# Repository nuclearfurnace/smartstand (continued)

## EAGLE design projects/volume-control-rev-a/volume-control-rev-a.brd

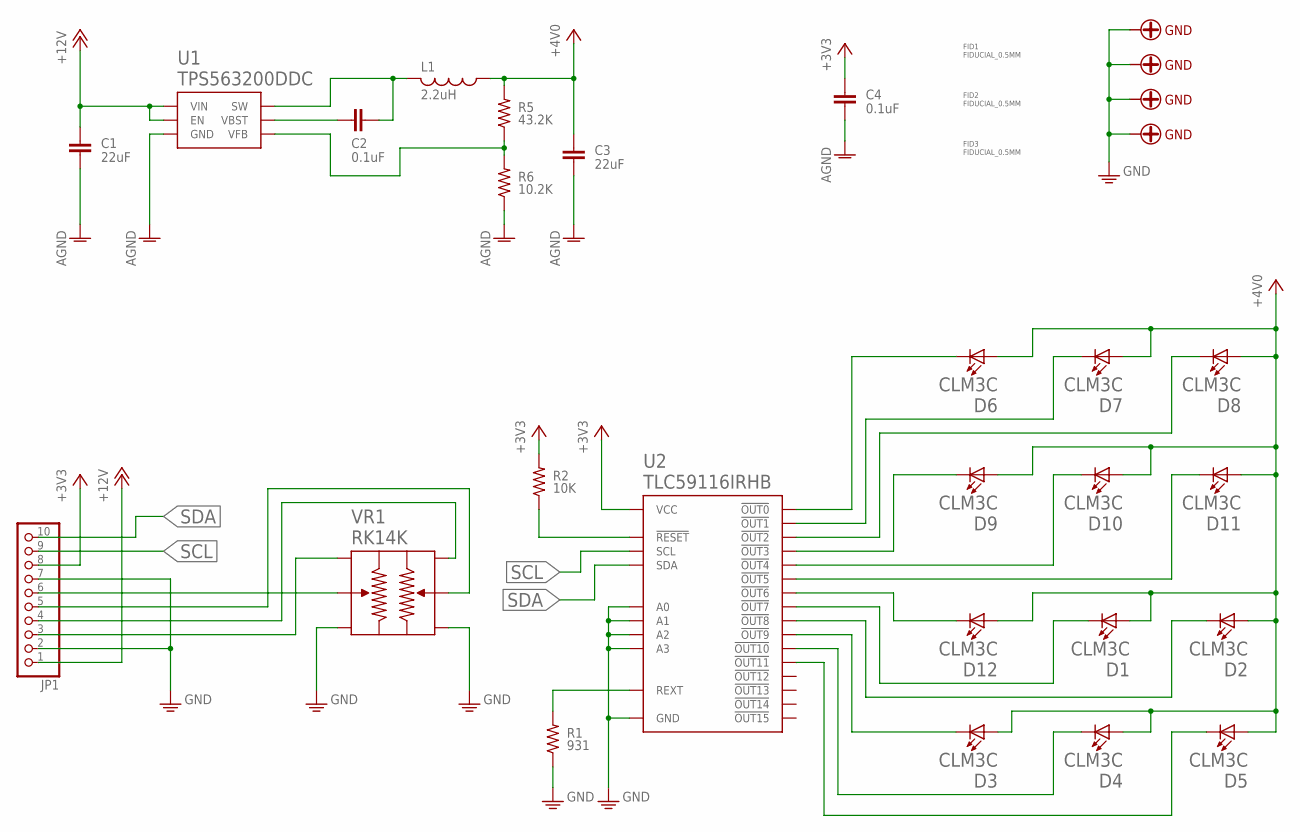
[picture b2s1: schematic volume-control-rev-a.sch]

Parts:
AGND: SCREW-THRU-GND-#4
C1, C3: 22uF; C1210
C2: 0.1uF; C0603
C4: 0.1uF; C0402
D1, D2, D3, D4, D5, D6, D7, D8, D9, D10, D11, D12: CLM3C; PLCC-2; MPN CLM3C-WKW-CXAYA453
FID1, FID2, FID3: FIDUCIAL_0.5MM
JP1: PINHD-1X10; 1X10; MPN 22-05-3101
L1: 2.2uH; COILCRAFT-XFL4020; MPN XFL4020-222MEB
R1: 931; R0402
R2: 10K; R0402
R5: 43.2K; R0402
R6: 10.2K; R0402
U1: TPS563200DDC; R-PDSO-G6-DBV; MPN TPS563200DDCT
U2: TLC59116IRHB; S-PVQFN-N32-RHB; MPN TLC59116IRHB
U$2, U$3, U$4: SCREW-THRU-GND-#4
VR1: RK14K

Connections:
+3V3: C4.1, JP1.8, R2.2, U2.P$27 (VCC)
+4V0: C3.1, D1.ANODE (A), D2.ANODE (A), D3.ANODE (A), D4.ANODE (A), D5.ANODE (A), D6.ANODE (A), D7.ANODE (A), D8.ANODE (A), D9.ANODE (A), D10.ANODE (A), D11.ANODE (A), D12.ANODE (A), L1.P$1 (1), R5.2
+12V: C1.1, JP1.1, U1.3 (VIN), U1.5 (EN)
AGND: C1.2, C3.2, C4.2, R6.1, U1.1 (GND)
GND: AGND.P$1, AGND.P$2, AGND.P$3, AGND.P$4, AGND.P$5, AGND.P$6, AGND.P$7, AGND.P$8, AGND.P$9, JP1.2, JP1.7, R1.1, U2.P$1 (A2), U2.P$2 (A3), U2.P$7 (GND), U2.P$18 (GND), U2.P$23 (GND), U2.P$31 (A0), U2.P$32 (A1), U2.P$EP (GND), U2.P$EP1 (GND), U2.P$EP2 (GND), U2.P$EP3 (GND), U2.P$EP4 (GND), U2.P$EP5 (GND), U$2.P$1, U$2.P$2, U$2.P$3, U$2.P$4, U$2.P$5, U$2.P$6, U$2.P$7, U$2.P$8, U$2.P$9, U$3.P$1, U$3.P$2, U$3.P$3, U$3.P$4, U$3.P$5, U$3.P$6, U$3.P$7, U$3.P$8, U$3.P$9, U$4.P$1, U$4.P$2, U$4.P$3, U$4.P$4, U$4.P$5, U$4.P$6, U$4.P$7, U$4.P$8, U$4.P$9, VR1.L3 (OUT_L), VR1.R3 (OUT_R)
LEFT_IN: JP1.3, VR1.L1 (IN_L)
LEFT_OUT: JP1.6, VR1.L2 (WIPER_L)
unnamed: D6.CATHODE (C), U2.P$3 (!OUT0)
unnamed: D7.CATHODE (C), U2.P$4 (!OUT1)
unnamed: D8.CATHODE (C), U2.P$5 (!OUT2)
unnamed: D3.CATHODE (C), U2.P$15 (!OUT9)
unnamed: D4.CATHODE (C), U2.P$16 (!OUT10)
unnamed: D5.CATHODE (C), U2.P$17 (!OUT11)
unnamed: D9.CATHODE (C), U2.P$6 (!OUT3)
unnamed: D10.CATHODE (C), U2.P$8 (!OUT4)
unnamed: D11.CATHODE (C), U2.P$9 (!OUT5)
unnamed: D12.CATHODE (C), U2.P$10 (!OUT6)
unnamed: D1.CATHODE (C), U2.P$11 (!OUT7)
unnamed: D2.CATHODE (C), U2.P$14 (!OUT8)
unnamed: C2.2, L1.P$2 (2), U1.2 (SW)
unnamed: C2.1, U1.6 (VBST)
unnamed: R5.1, R6.2, U1.4 (VFB)
unnamed: R2.1, U2.P$24 (!RESET)
unnamed: R1.2, U2.P$30 (REXT)
RIGHT_IN: JP1.4, VR1.R1 (IN_R)
RIGHT_OUT: JP1.5, VR1.R2 (WIPER_R)
SCL: JP1.9, U2.P$25 (SCL)
SDA: JP1.10, U2.P$26 (SDA)

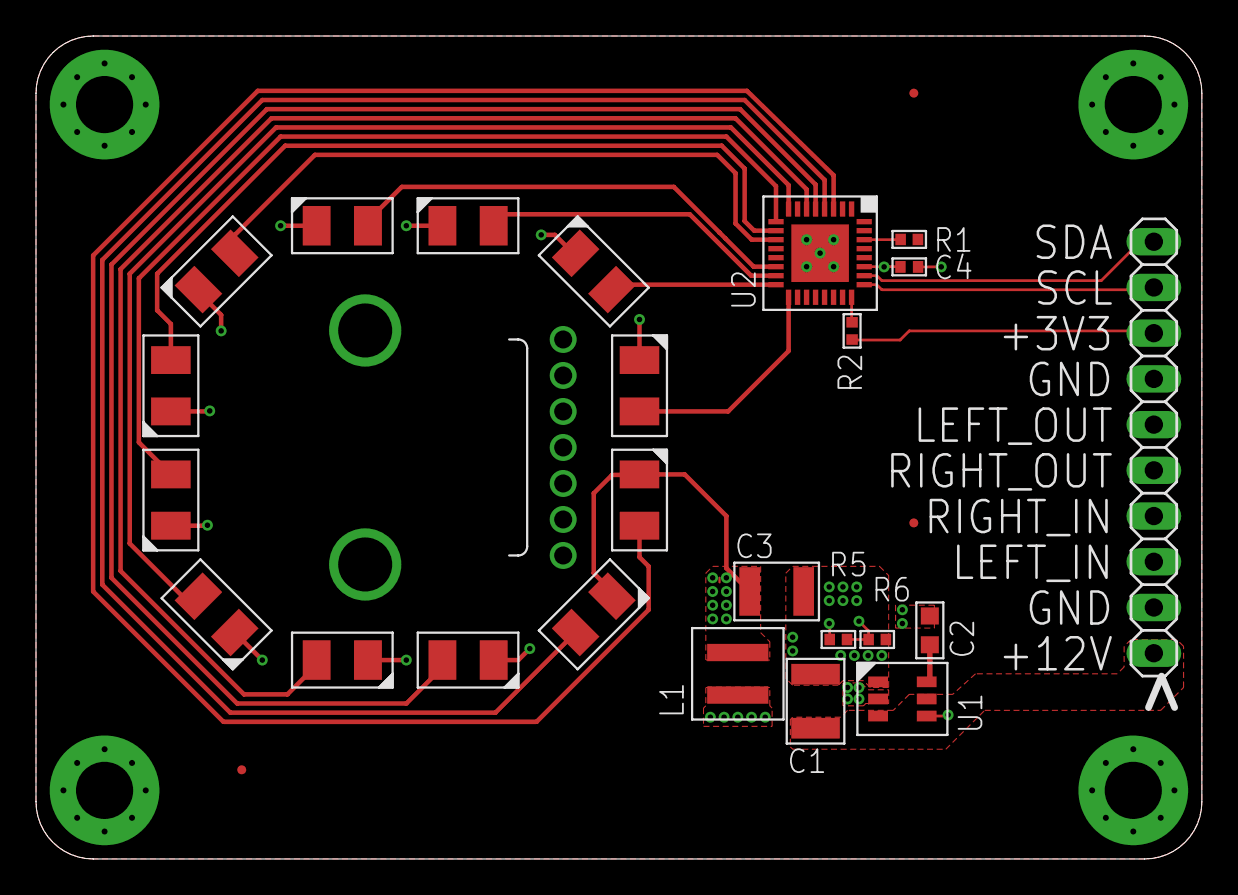
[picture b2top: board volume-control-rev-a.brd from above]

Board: 4 copper layers, 64.8 x 45.7 mm, 33 parts (1 on the bottom side), 28 nets.

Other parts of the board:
U$1: NF_LOGO

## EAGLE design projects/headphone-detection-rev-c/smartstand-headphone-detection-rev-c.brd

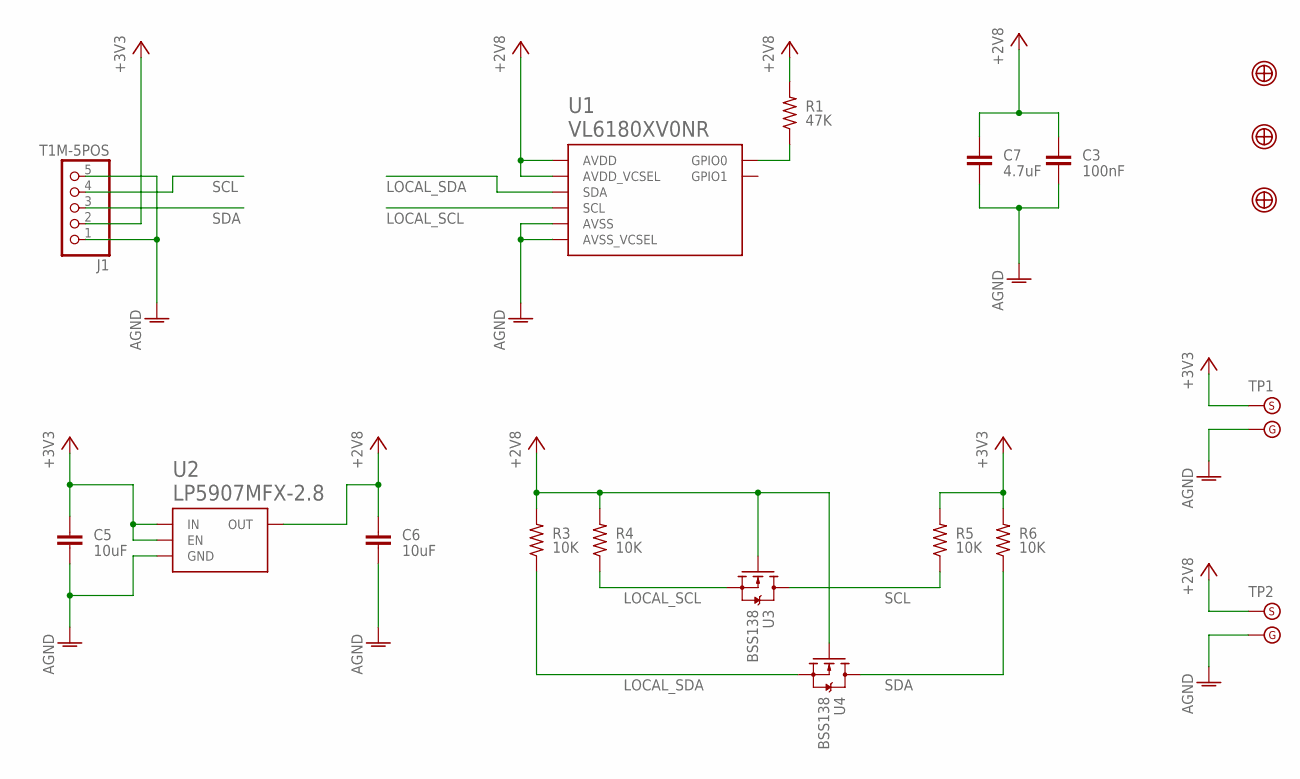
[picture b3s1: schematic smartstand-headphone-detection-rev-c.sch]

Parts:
C3: 100nF; C0402
C5, C6: 10uF; C0603
C7: 4.7uF; C0603
J1: T1M-5POS; T1M-SINGLE-5POS
R1: 47K; R0402
R3, R4, R5, R6: 10K; R0402
TP1, TP2: TESTPOINT-WITH-GND; TESTPOINT-1.5-WITH-GND
U1: VL6180XV0NR; VL6180X
U2: LP5907MFX-2.8; R-PDSO-G5-DBV
U3, U4: BSS138; SOT23
U$1, U$2, U$3: FIDUCIAL-1MM; FIDUCIAL_1MM

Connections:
+2V8: C3.1, C6.1, C7.1, R1.2, R3.2, R4.2, TP2.S, U1.8 (AVDD_VCSEL), U1.10 (AVDD), U2.5 (OUT), U3.1 (G), U4.1 (G)
+3V3: C5.1, J1.2, R5.2, R6.2, TP1.S, U2.1 (IN), U2.3 (EN)
AGND: C3.2, C5.2, C6.2, C7.2, J1.1, J1.5, TP1.G, TP2.G, U1.9 (AVSS_VCSEL), U1.12 (AVSS), U2.2 (GND)
LOCAL_SCL: R4.1, U1.5 (SCL), U3.2 (S)
LOCAL_SDA: R3.1, U1.6 (SDA), U4.2 (S)
unnamed: R1.1, U1.4 (GPIO0)
SCL: J1.4, R5.1, U3.3 (D)
SDA: J1.3, R6.1, U4.3 (D)

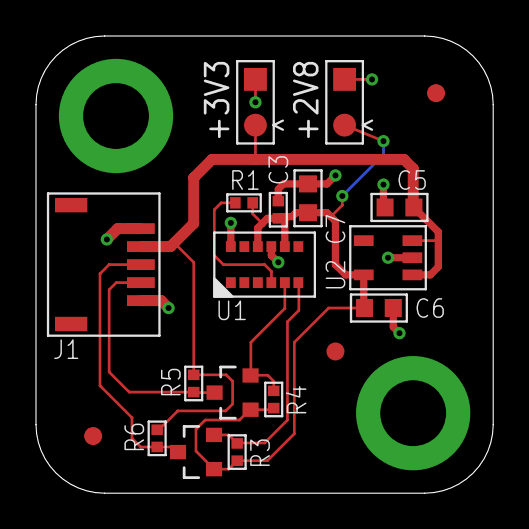
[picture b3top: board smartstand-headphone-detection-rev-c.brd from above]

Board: 2 copper layers, 25.4 x 25.4 mm, 19 parts (0 on the bottom side), 8 nets.

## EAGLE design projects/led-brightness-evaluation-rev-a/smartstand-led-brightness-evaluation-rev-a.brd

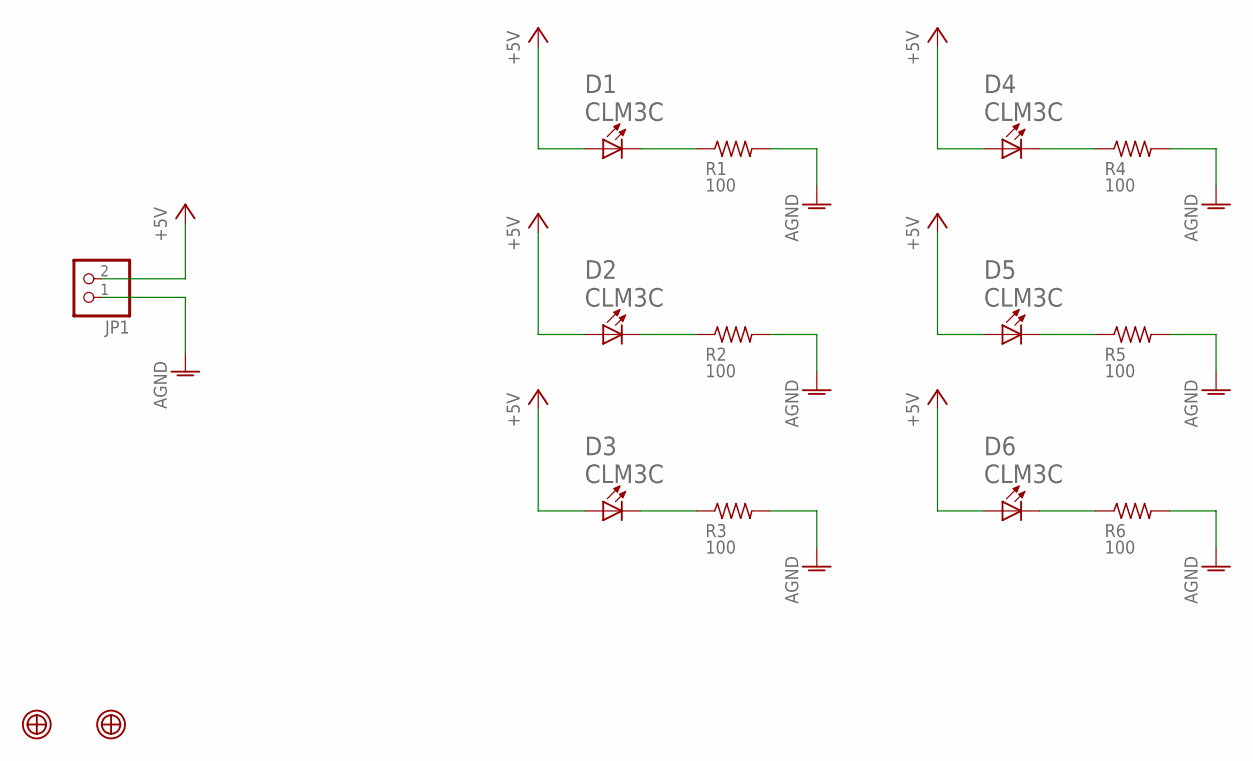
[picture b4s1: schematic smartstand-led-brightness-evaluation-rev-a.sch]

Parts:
D1, D2, D3, D4, D5, D6: CLM3C; PLCC-2
JP1: PINHD-1X2; 1X02
R1, R2, R3, R4, R5, R6: 100; R0805
U$1, U$2: FIDUCIAL-1MM; FIDUCIAL_1MM

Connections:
+5V: D1.ANODE (A), D2.ANODE (A), D3.ANODE (A), D4.ANODE (A), D5.ANODE (A), D6.ANODE (A), JP1.2
AGND: JP1.1, R1.2, R2.2, R3.2, R4.2, R5.2, R6.2
unnamed: D1.CATHODE (C), R1.1
unnamed: D2.CATHODE (C), R2.1
unnamed: D3.CATHODE (C), R3.1
unnamed: D4.CATHODE (C), R4.1
unnamed: D5.CATHODE (C), R5.1
unnamed: D6.CATHODE (C), R6.1

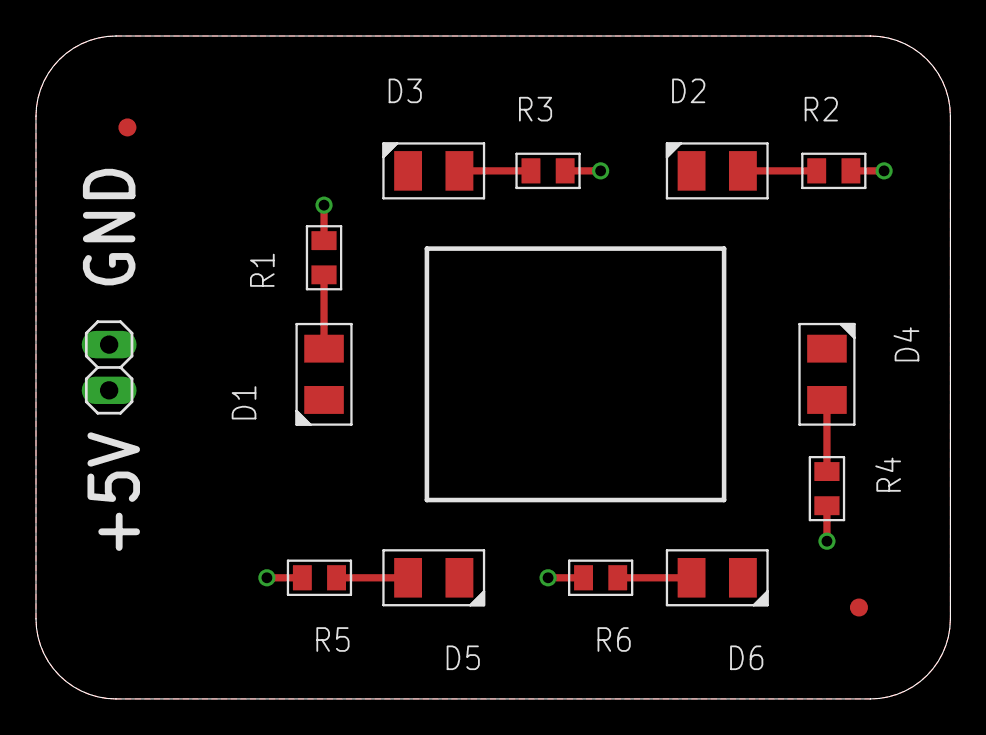
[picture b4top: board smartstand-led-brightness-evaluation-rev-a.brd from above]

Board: 2 copper layers, 50.8 x 36.8 mm, 15 parts (0 on the bottom side), 8 nets.

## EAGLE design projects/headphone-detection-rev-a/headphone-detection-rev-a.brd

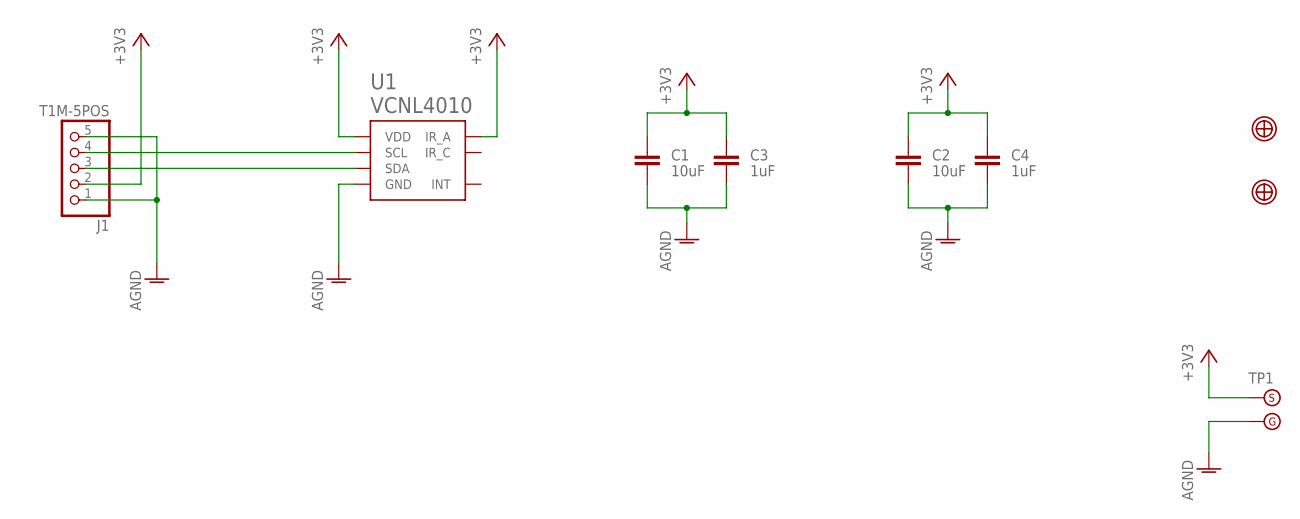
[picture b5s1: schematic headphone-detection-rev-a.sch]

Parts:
C1, C2: 10uF; C0603
C3, C4: 1uF; C0402
J1: T1M-5POS; T1M-SINGLE-5POS
TP1: TESTPOINT-WITH-GND; TESTPOINT-1.5-WITH-GND
U1: VCNL4010
U$1, U$2: FIDUCIAL-1MM; FIDUCIAL_1MM

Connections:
+3V3: C1.1, C2.1, C3.1, C4.1, J1.2, TP1.S, U1.IR_ANODE (IR_A), U1.VDD
AGND: C1.2, C2.2, C3.2, C4.2, J1.1, J1.5, TP1.G, U1.GND1 (GND), U1.GND2 (GND)
unnamed: J1.4, U1.SCL
unnamed: J1.3, U1.SDA

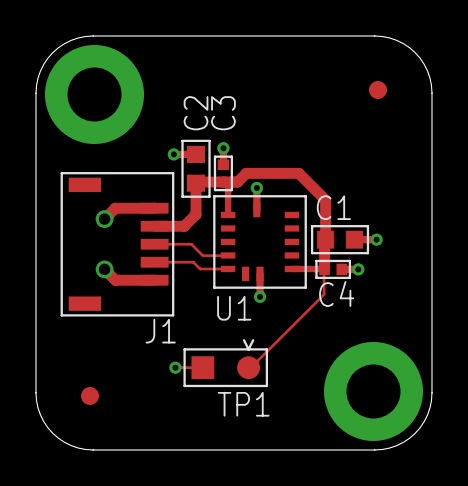
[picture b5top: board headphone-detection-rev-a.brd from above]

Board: 2 copper layers, 22.0 x 23.0 mm, 9 parts (0 on the bottom side), 4 nets.

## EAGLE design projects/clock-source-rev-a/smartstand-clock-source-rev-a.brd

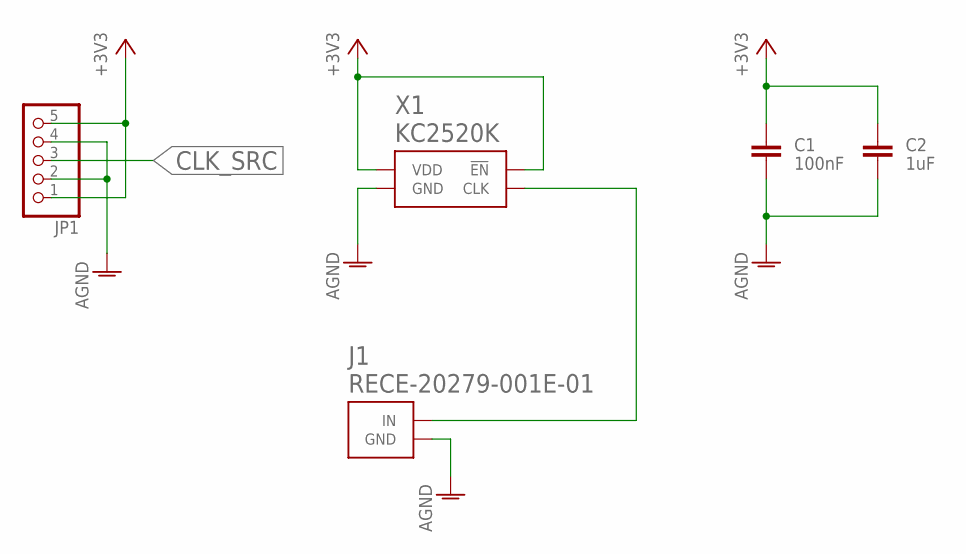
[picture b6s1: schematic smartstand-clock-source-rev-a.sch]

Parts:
C1: 100nF; C0402
C2: 1uF; C0603
J1: RECE-20279-001E-01; IPEX-MHF
JP1: PINHD-1X5; 1X05
X1: KC2520K; KC2520C

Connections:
+3V3: C1.1, C2.1, JP1.1, JP1.5, X1.P$1 (!EN), X1.P$4 (VDD)
AGND: C1.2, C2.2, J1.P$1 (GND), J1.P$2 (GND), JP1.2, JP1.4, X1.P$2 (GND)
CLK_SRC: JP1.3
unnamed: J1.P$3 (IN), X1.P$3 (CLK)

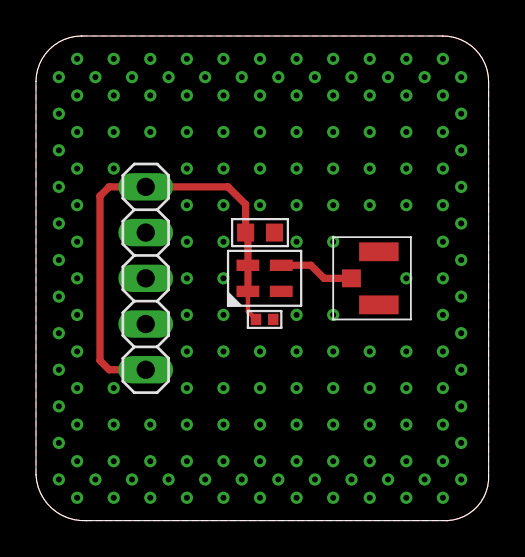
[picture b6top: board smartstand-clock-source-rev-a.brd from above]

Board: 2 copper layers, 25.1 x 26.9 mm, 5 parts (0 on the bottom side), 3 nets.

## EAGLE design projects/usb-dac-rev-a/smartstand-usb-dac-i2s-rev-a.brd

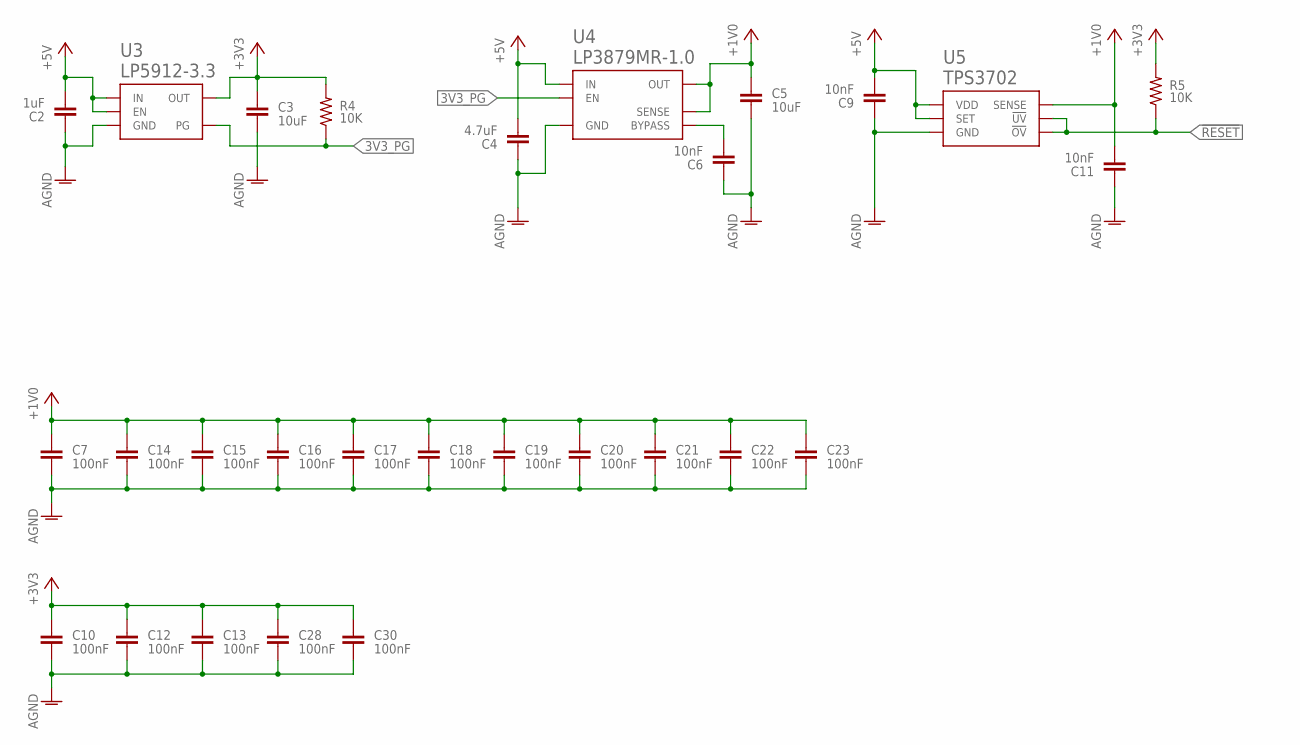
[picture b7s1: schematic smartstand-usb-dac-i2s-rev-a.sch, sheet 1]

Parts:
C2: 1uF; C0603
C3, C5: 10uF; C0603
C4: 4.7uF; C0603
C6, C9, C11: 10nF; C0402
C7, C10, C12, C13, C14, C15, C16, C17, C18, C19, C20, C21, C22, C23, C28, C30: 100nF; C0402
R4, R5: 10K; R0402
U3: LP5912-3.3; P-PWSON-N6
U4: LP3879MR-1.0; PSOP-8-POWERPAD-DDA
U5: TPS3702; R-PDSO-G6

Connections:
3V3_PG: R4.1, U3.P$3 (PG), U4.8 (EN); also elsewhere on the board
!RESET: R5.1, U5.1 (!UV), U5.6 (!OV); also elsewhere on the board
+1V0: C5.1, C7.1, C11.2, C14.1, C15.1, C16.1, C17.1, C18.1, C19.1, C20.1, C21.1, C22.1, C23.1, U4.5 (OUT), U4.6 (SENSE), U5.3 (SENSE); also elsewhere on the board
+3V3: C3.1, C10.1, C12.1, C13.1, C28.1, C30.1, R4.2, R5.2, U3.P$1 (OUT); also elsewhere on the board
+5V: C2.2, C4.2, C9.2, U3.P$4 (EN), U3.P$6 (IN), U4.4 (IN), U5.4 (SET), U5.5 (VDD); also elsewhere on the board
AGND: C2.1, C3.2, C4.1, C5.2, C6.1, C7.2, C9.1, C10.2, C11.1, C12.2, C13.2, C14.2, C15.2, C16.2, C17.2, C18.2, C19.2, C20.2, C21.2, C22.2, C23.2, C28.2, C30.2, U3.P$5 (GND), U3.P$8 (GND), U3.P$9 (GND), U3.P$EP (GND), U4.3 (GND), U4.EP (GND), U4.P$1 (GND), U4.P$2 (GND), U4.P$3 (GND), U4.P$4 (GND), U4.P$5 (GND), U4.P$6 (GND), U5.2 (GND); also elsewhere on the board
unnamed: C6.2, U4.1 (BYPASS)

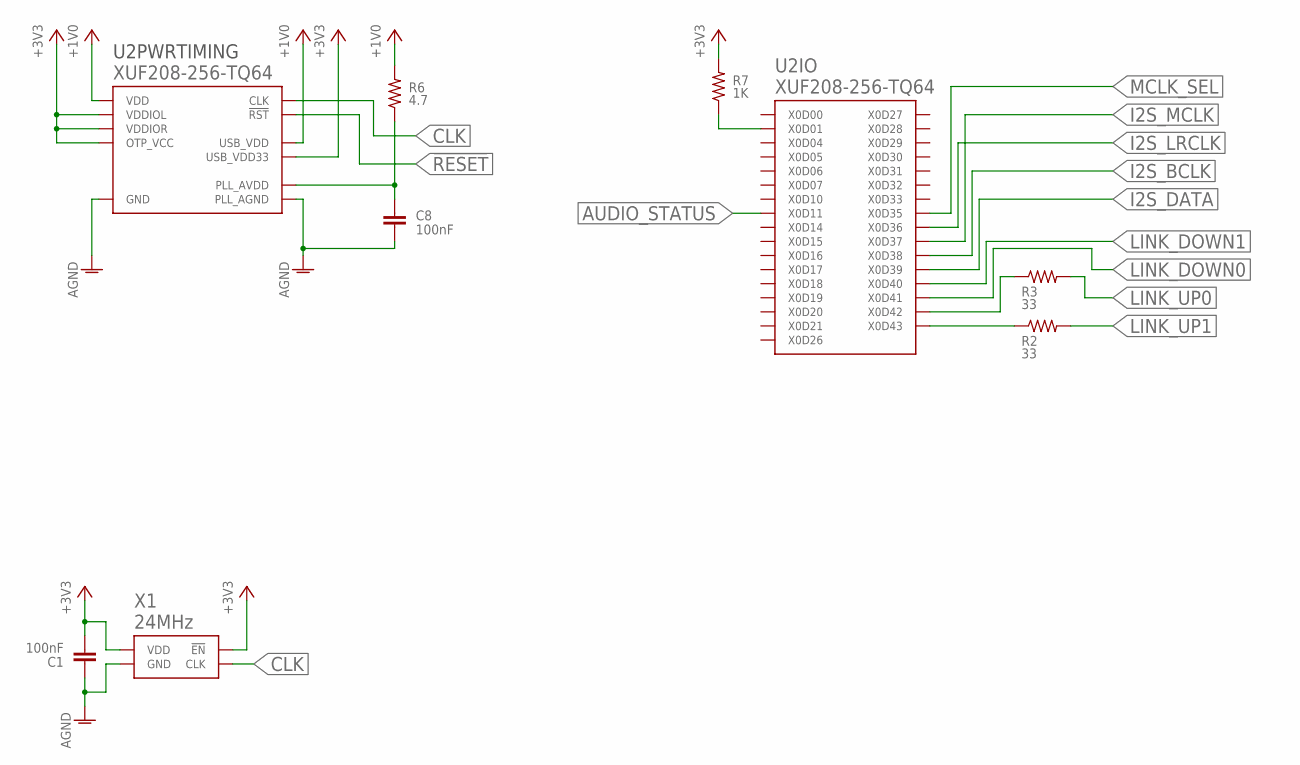
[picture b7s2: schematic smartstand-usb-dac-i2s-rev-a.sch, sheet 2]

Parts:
C1, C8: 100nF; C0402
R2, R3: 33; R0402
R6: 4.7; R0402
R7: 1K; R0402
U2: XUF208-256-TQ64; TQFP-64-EXPOSED-PAD
X1: 24MHz; KC2520C

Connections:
!RESET: U2.P$57 (!RST); also elsewhere on the board
+1V0: R6.2, U2.P$9 (VDD), U2.P$10 (VDD), U2.P$20 (VDD), U2.P$27 (USB_VDD), U2.P$31 (VDD), U2.P$39 (VDD), U2.P$40 (VDD), U2.P$41 (VDD), U2.P$52 (VDD), U2.P$56 (VDD), U2.P$59 (VDD); also elsewhere on the board
+3V3: C1.2, R7.2, U2.P$3 (VDDIOL), U2.P$13 (VDDIOL), U2.P$22 (USB_VDD33), U2.P$34 (VDDIOR), U2.P$44 (VDDIOR), U2.P$55 (OTP_VCC), X1.P$1 (!EN), X1.P$4 (VDD); also elsewhere on the board
AGND: C1.1, C8.2, U2.P$54 (PLL_AGND), U2.P$65 (GND), U2.P$66 (GND), U2.P$67 (GND), U2.P$68 (GND), U2.P$69 (GND), U2.P$70 (GND), U2.P$71 (GND), U2.P$72 (GND), U2.P$73 (GND), U2.P$74 (GND), X1.P$2 (GND); also elsewhere on the board
AUDIO_STATUS: U2.P$16 (X0D11); also elsewhere on the board
CLK: U2.P$58 (CLK), X1.P$3 (CLK); also elsewhere on the board
I2S_BCLK: U2.P$2 (X0D38); also elsewhere on the board
I2S_DATA: U2.P$4 (X0D39); also elsewhere on the board
I2S_LRCLK: U2.P$1 (X0D36); also elsewhere on the board
I2S_MCLK: U2.P$64 (X0D37); also elsewhere on the board
LINK_DOWN0: U2.P$6 (X0D41); also elsewhere on the board
LINK_DOWN1: U2.P$5 (X0D40); also elsewhere on the board
LINK_UP0: R3.2; also elsewhere on the board
LINK_UP1: R2.2; also elsewhere on the board
MCLK_SEL: U2.P$42 (X0D35); also elsewhere on the board
unnamed: C8.1, R6.1, U2.P$53 (PLL_AVDD)
unnamed: R3.1, U2.P$7 (X0D42)
unnamed: R2.1, U2.P$8 (X0D43)
unnamed: R7.1, U2.P$11 (X0D01)

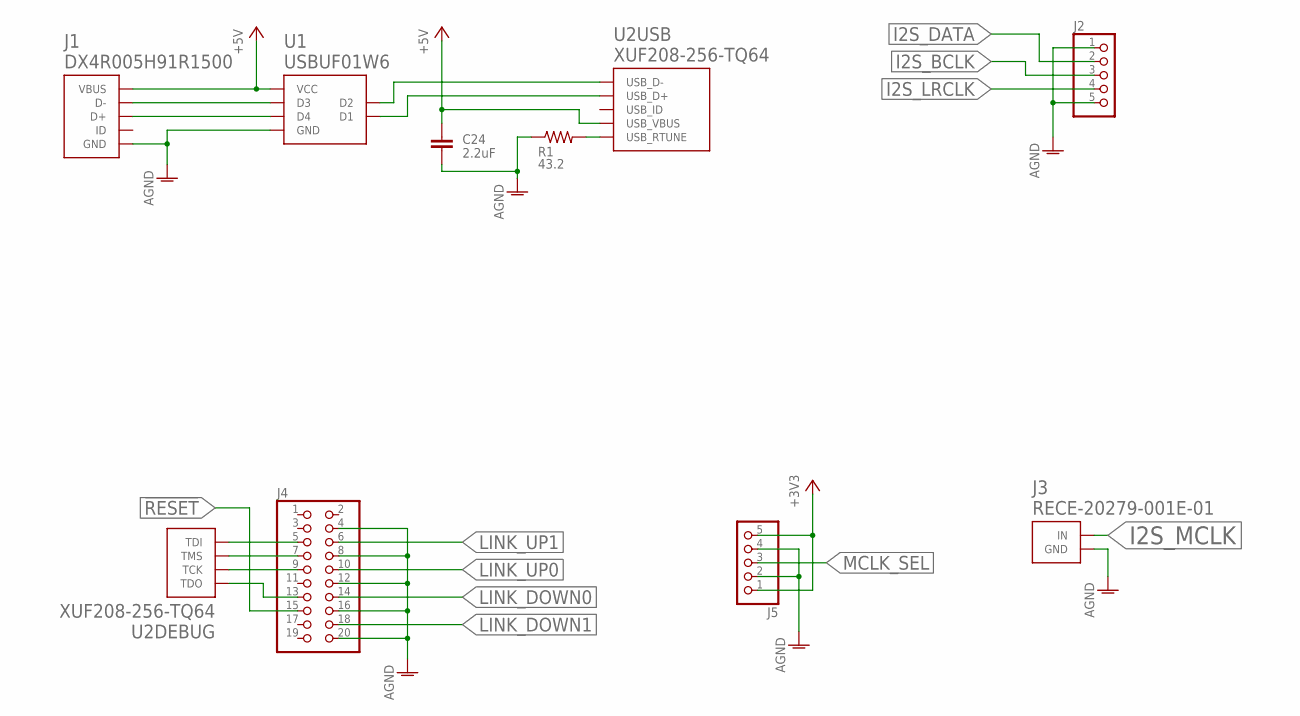
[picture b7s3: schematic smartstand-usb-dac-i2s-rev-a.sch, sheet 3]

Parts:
C24: 2.2uF; C0603
J1: DX4R005H91R1500
J2, J5: PINHD-1X5; 1X05
J3: RECE-20279-001E-01; IPEX-MHF
J4: PINHD-2X10; 2X10
R1: 43.2; R0402
U1: USBUF01W6; SOT323-6L
U2: XUF208-256-TQ64; TQFP-64-EXPOSED-PAD

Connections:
!RESET: J4.15; also elsewhere on the board
+3V3: J5.1, J5.5; also elsewhere on the board
+5V: C24.1, J1.P$1 (VBUS), U1.P$5 (VCC), U2.P$23 (USB_VBUS); also elsewhere on the board
AGND: C24.2, J1.P$5 (GND), J2.1, J2.5, J3.P$1 (GND), J3.P$2 (GND), J4.4, J4.8, J4.12, J4.16, J4.20, J5.2, J5.4, R1.1, U1.P$2 (GND); also elsewhere on the board
CLEAN_USB_D_N: U1.P$3 (D2), U2.P$26 (USB_D-)
CLEAN_USB_D_P: U1.P$1 (D1), U2.P$25 (USB_D+)
I2S_BCLK: J2.3; also elsewhere on the board
I2S_DATA: J2.2; also elsewhere on the board
I2S_LRCLK: J2.4; also elsewhere on the board
I2S_MCLK: J3.P$3 (IN); also elsewhere on the board
LINK_DOWN0: J4.14; also elsewhere on the board
LINK_DOWN1: J4.18; also elsewhere on the board
LINK_UP0: J4.10; also elsewhere on the board
LINK_UP1: J4.6; also elsewhere on the board
MCLK_SEL: J5.3; also elsewhere on the board
unnamed: R1.2, U2.P$24 (USB_RTUNE)
unnamed: J4.7, U2.P$60 (TMS)
unnamed: J4.9, U2.P$61 (TCK)
unnamed: J4.5, U2.P$62 (TDI)
unnamed: J4.13, U2.P$63 (TDO)
RAW_USB_D_N: J1.P$2 (D-), U1.P$4 (D3)
RAW_USB_D_P: J1.P$3 (D+), U1.P$6 (D4)

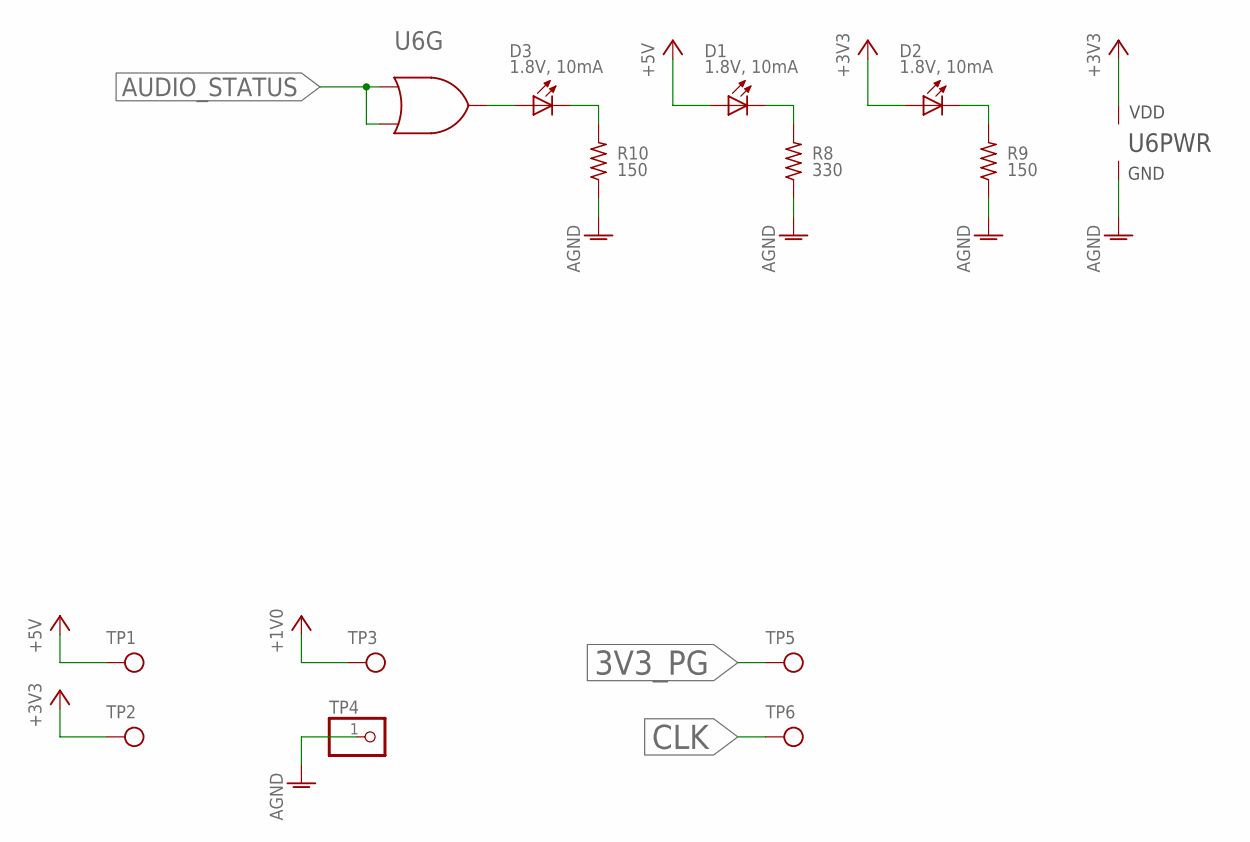
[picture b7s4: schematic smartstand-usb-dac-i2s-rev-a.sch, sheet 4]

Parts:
D1, D2, D3: 1.8V, 10mA; DIALIGHT-0603
R8: 330; R0402
R9, R10: 150; R0402
TP1, TP2, TP3, TP5, TP6: TESTPOINT-1.5MM; TESTPOINT-1.5
TP4: PINHD-1X1; 1X01
U6: SN74LVC1G32DRL; R-PDSO-N5

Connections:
3V3_PG: TP5.P$1; also elsewhere on the board
+1V0: TP3.P$1; also elsewhere on the board
+3V3: D2.1 (A), TP2.P$1, U6.5 (VDD); also elsewhere on the board
+5V: D1.1 (A), TP1.P$1; also elsewhere on the board
AGND: R8.1, R9.1, R10.1, TP4.1, U6.3 (GND); also elsewhere on the board
AUDIO_STATUS: U6.1 (A), U6.2 (B); also elsewhere on the board
CLK: TP6.P$1; also elsewhere on the board
unnamed: D1.2 (C), R8.2
unnamed: D2.2 (C), R9.2
unnamed: D3.1 (A), U6.4 (Q)
unnamed: D3.2 (C), R10.2

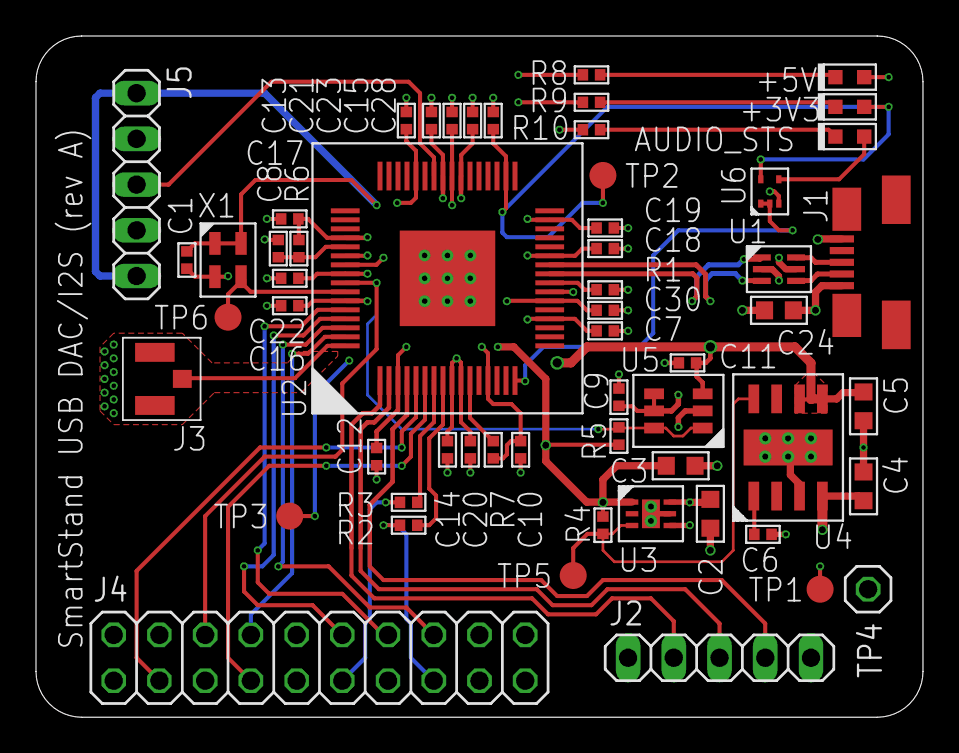
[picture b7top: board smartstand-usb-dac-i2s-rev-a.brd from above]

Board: 4 copper layers, 49.3 x 37.8 mm, 57 parts (0 on the bottom side), 35 nets.

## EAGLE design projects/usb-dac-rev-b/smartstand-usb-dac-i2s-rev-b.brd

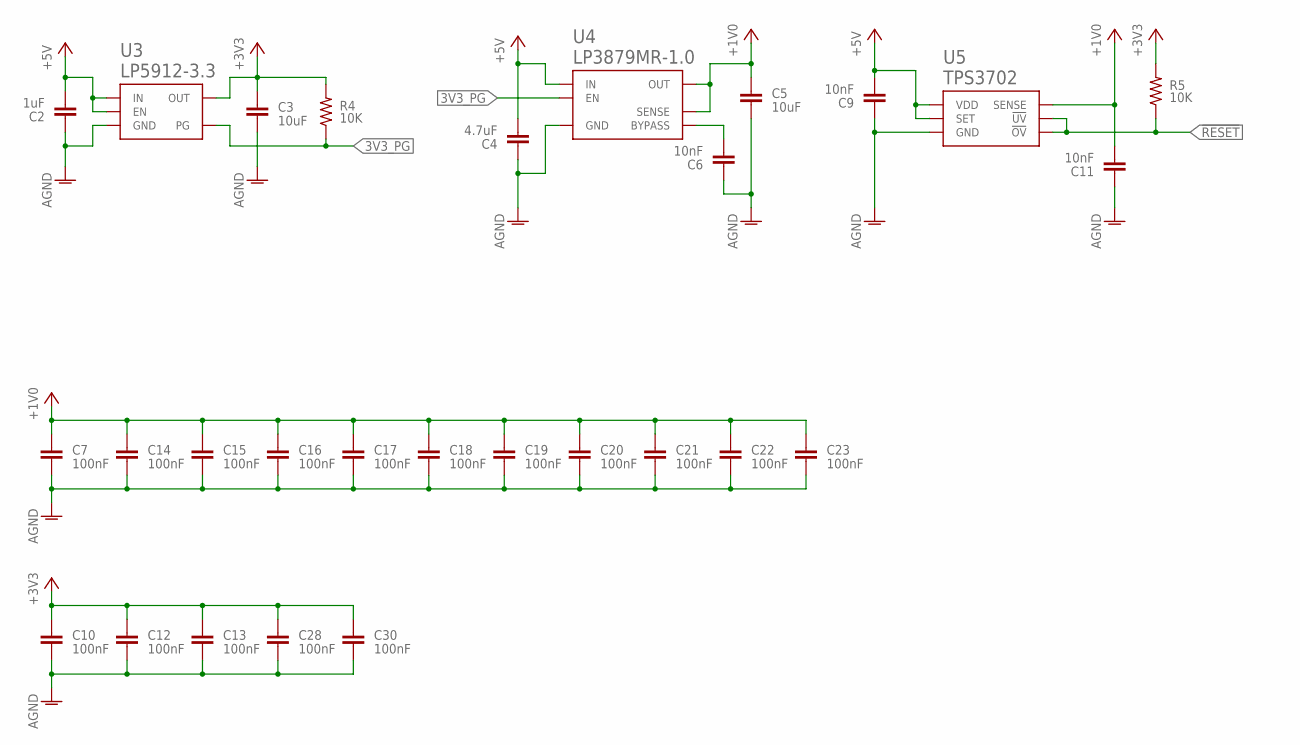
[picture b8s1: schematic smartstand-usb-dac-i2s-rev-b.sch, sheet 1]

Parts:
C2: 1uF; C0603
C3, C5: 10uF; C0603
C4: 4.7uF; C0603
C6, C9, C11: 10nF; C0402
C7, C10, C12, C13, C14, C15, C16, C17, C18, C19, C20, C21, C22, C23, C28, C30: 100nF; C0402
R4, R5: 10K; R0402
U3: LP5912-3.3; P-PWSON-N6
U4: LP3879MR-1.0; PSOP-8-POWERPAD-DDA
U5: TPS3702; R-PDSO-G6

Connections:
3V3_PG: R4.1, U3.P$3 (PG), U4.8 (EN)
!RESET: R5.1, U5.1 (!UV), U5.6 (!OV); also elsewhere on the board
+1V0: C5.1, C7.1, C11.2, C14.1, C15.1, C16.1, C17.1, C18.1, C19.1, C20.1, C21.1, C22.1, C23.1, U4.5 (OUT), U4.6 (SENSE), U5.3 (SENSE); also elsewhere on the board
+3V3: C3.1, C10.1, C12.1, C13.1, C28.1, C30.1, R4.2, R5.2, U3.P$1 (OUT); also elsewhere on the board
+5V: C2.2, C4.2, C9.2, U3.P$4 (EN), U3.P$6 (IN), U4.4 (IN), U5.4 (SET), U5.5 (VDD); also elsewhere on the board
AGND: C2.1, C3.2, C4.1, C5.2, C6.1, C7.2, C9.1, C10.2, C11.1, C12.2, C13.2, C14.2, C15.2, C16.2, C17.2, C18.2, C19.2, C20.2, C21.2, C22.2, C23.2, C28.2, C30.2, U3.P$5 (GND), U3.P$8 (GND), U3.P$9 (GND), U3.P$EP (GND), U4.3 (GND), U4.EP (GND), U4.P$1 (GND), U4.P$2 (GND), U4.P$3 (GND), U4.P$4 (GND), U4.P$5 (GND), U4.P$6 (GND), U5.2 (GND); also elsewhere on the board
unnamed: C6.2, U4.1 (BYPASS)

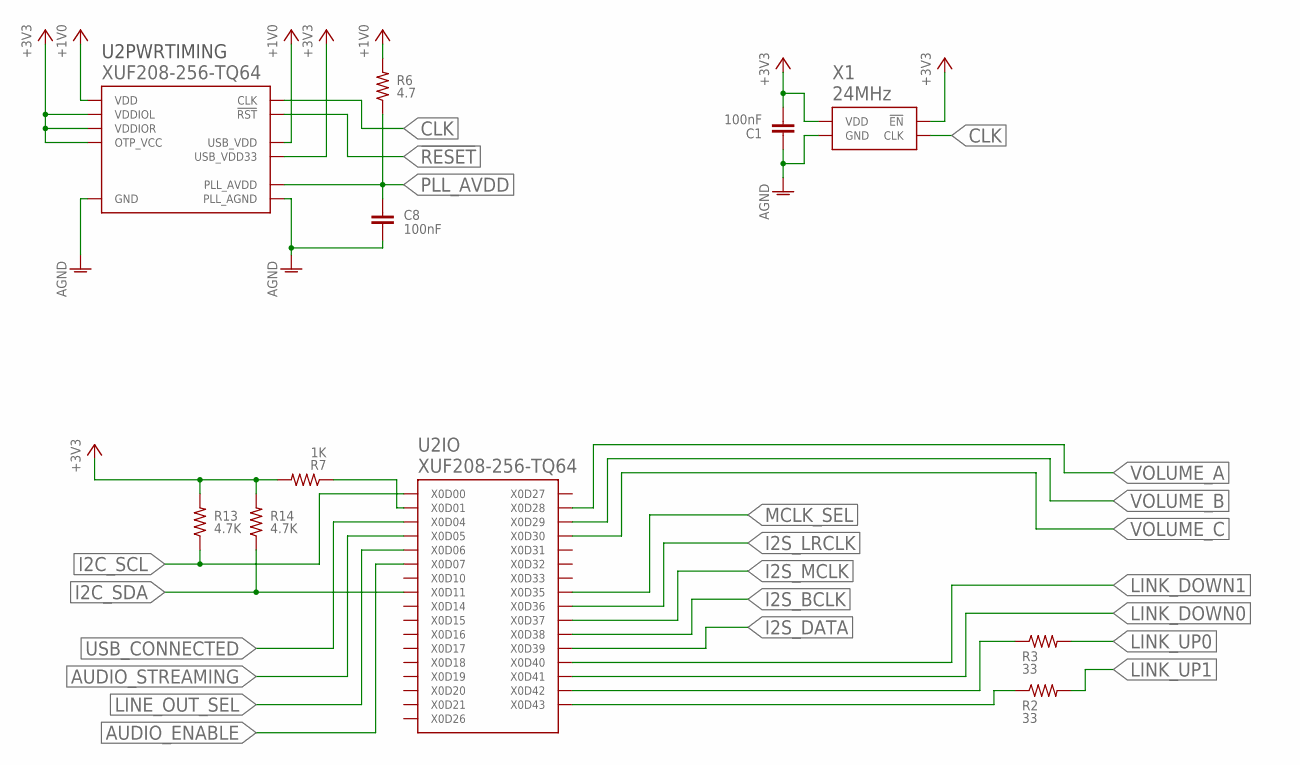
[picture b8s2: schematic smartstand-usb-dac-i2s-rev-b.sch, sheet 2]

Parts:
C1, C8: 100nF; C0402
R2, R3: 33; R0402
R6: 4.7; R0402
R7: 1K; R0402
R13, R14: 4.7K; R0402
U2: XUF208-256-TQ64; TQFP-64-EXPOSED-PAD
X1: 24MHz; KC2520C

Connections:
!RESET: U2.P$57 (!RST); also elsewhere on the board
+1V0: R6.2, U2.P$9 (VDD), U2.P$10 (VDD), U2.P$20 (VDD), U2.P$27 (USB_VDD), U2.P$31 (VDD), U2.P$39 (VDD), U2.P$40 (VDD), U2.P$41 (VDD), U2.P$52 (VDD), U2.P$56 (VDD), U2.P$59 (VDD); also elsewhere on the board
+3V3: C1.2, R7.2, R13.2, R14.2, U2.P$3 (VDDIOL), U2.P$13 (VDDIOL), U2.P$22 (USB_VDD33), U2.P$34 (VDDIOR), U2.P$44 (VDDIOR), U2.P$55 (OTP_VCC), X1.P$1 (!EN), X1.P$4 (VDD); also elsewhere on the board
AGND: C1.1, C8.2, U2.P$54 (PLL_AGND), U2.P$65 (GND), U2.P$66 (GND), U2.P$67 (GND), U2.P$68 (GND), U2.P$69 (GND), U2.P$70 (GND), U2.P$71 (GND), U2.P$72 (GND), U2.P$73 (GND), U2.P$74 (GND), X1.P$2 (GND); also elsewhere on the board
AUDIO_ENABLE: U2.P$19 (X0D07); also elsewhere on the board
AUDIO_STREAMING: U2.P$17 (X0D05); also elsewhere on the board
CLK: U2.P$58 (CLK), X1.P$3 (CLK); also elsewhere on the board
I2C_SCL: R13.1, U2.P$14 (X0D00); also elsewhere on the board
I2C_SDA: R14.1, U2.P$16 (X0D11); also elsewhere on the board
I2S_BCLK: U2.P$2 (X0D38); also elsewhere on the board
I2S_DATA: U2.P$4 (X0D39); also elsewhere on the board
I2S_LRCLK: U2.P$1 (X0D36); also elsewhere on the board
I2S_MCLK: U2.P$64 (X0D37); also elsewhere on the board
LINE_OUT_SEL: U2.P$18 (X0D06); also elsewhere on the board
LINK_DOWN0: U2.P$6 (X0D41); also elsewhere on the board
LINK_DOWN1: U2.P$5 (X0D40); also elsewhere on the board
LINK_UP0: R3.2; also elsewhere on the board
LINK_UP1: R2.2; also elsewhere on the board
MCLK_SEL: U2.P$42 (X0D35); also elsewhere on the board
unnamed: R3.1, U2.P$7 (X0D42)
unnamed: R2.1, U2.P$8 (X0D43)
unnamed: R7.1, U2.P$11 (X0D01)
PLL_AVDD: C8.1, R6.1, U2.P$53 (PLL_AVDD); also elsewhere on the board
USB_CONNECTED: U2.P$15 (X0D04); also elsewhere on the board
VOLUME_A: U2.P$47 (X0D28); also elsewhere on the board
VOLUME_B: U2.P$49 (X0D29); also elsewhere on the board
VOLUME_C: U2.P$50 (X0D30); also elsewhere on the board
